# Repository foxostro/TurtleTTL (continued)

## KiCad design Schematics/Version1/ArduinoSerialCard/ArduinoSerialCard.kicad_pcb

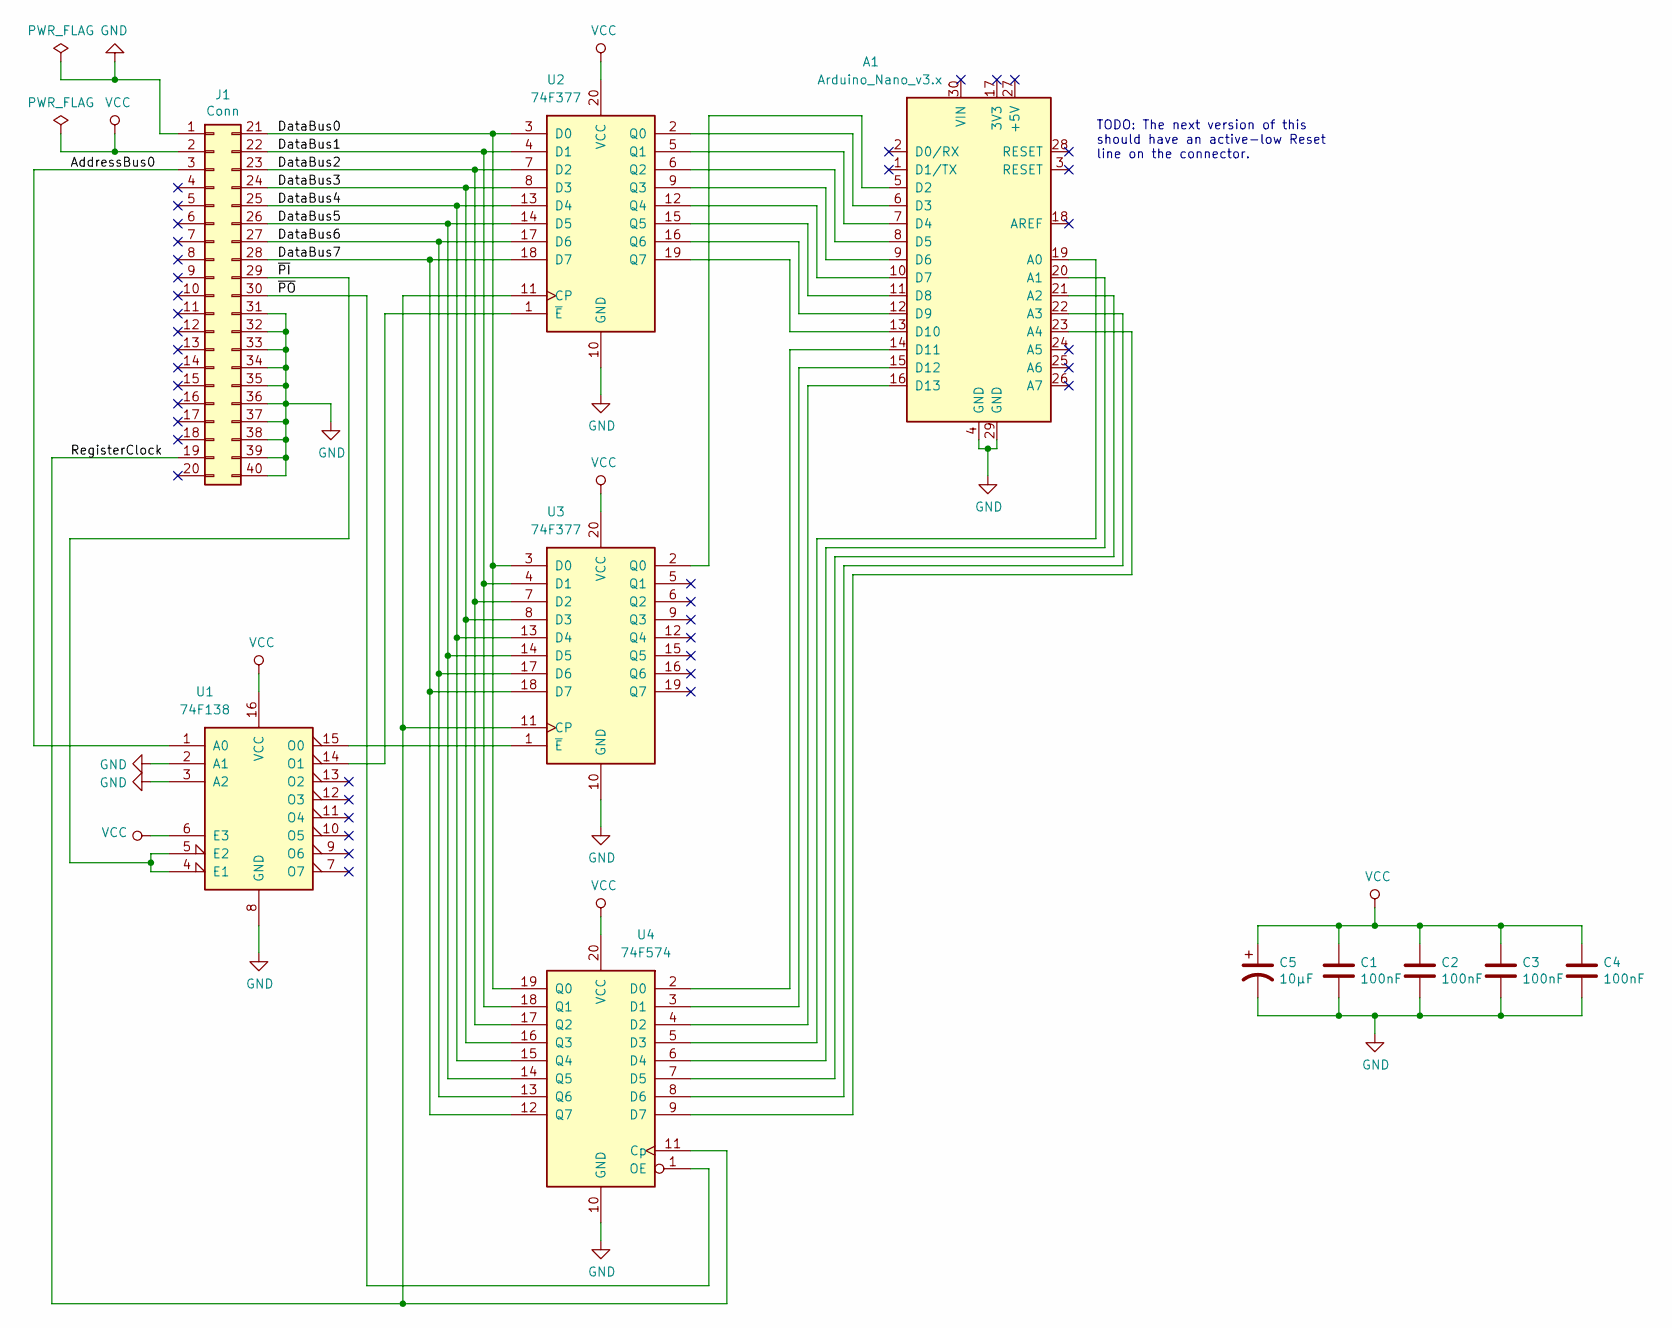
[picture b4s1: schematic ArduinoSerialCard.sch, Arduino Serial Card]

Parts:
A1: Arduino_Nano_v3.x; Arduino_Nano
C1, C2, C3, C4: 100nF; C_Disc_D4.3mm_W1.9mm_P5.00mm
C5: 10µF; CP_Radial_D5.0mm_P2.00mm
J1: Conn; PinSocket_2x20_P2.54mm_Vertical
U1: 74F138; DIP-16_W7.62mm
U2, U3: 74F377; DIP-20_W7.62mm
U4: 74F574; DIP-20_W7.62mm

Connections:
/AddressBus0: J1.3, U1.1 (A0)
/DataBus0: J1.21, U2.3 (D0), U3.3 (D0), U4.19 (Q0)
/DataBus1: J1.22, U2.4 (D1), U3.4 (D1), U4.18 (Q1)
/DataBus2: J1.23, U2.7 (D2), U3.7 (D2), U4.17 (Q2)
/DataBus3: J1.24, U2.8 (D3), U3.8 (D3), U4.16 (Q3)
/DataBus4: J1.25, U2.13 (D4), U3.13 (D4), U4.15 (Q4)
/DataBus5: J1.26, U2.14 (D5), U3.14 (D5), U4.14 (Q5)
/DataBus6: J1.27, U2.17 (D6), U3.17 (D6), U4.13 (Q6)
/DataBus7: J1.28, U2.18 (D7), U3.18 (D7), U4.12 (Q7)
/RegisterClock: J1.19, U2.11 (CP), U3.11 (CP), U4.11 (Cp)
/~PI: J1.29, U1.4 (E1), U1.5 (E2)
/~PO: J1.30, U4.1 (OE)
GND: A1.4 (GND), A1.29 (GND), C1.2, C2.2, C3.2, C4.2, C5.2, J1.1, J1.31, J1.32, J1.33, J1.34, J1.35, J1.36, J1.37, J1.38, J1.39, J1.40, U1.2 (A1), U1.3 (A2), U1.8 (GND), U2.10 (GND), U3.10 (GND), U4.10 (GND)
unnamed: A1.5 (D2), U3.2 (Q0)
unnamed: A1.6 (D3), U2.2 (Q0)
unnamed: A1.7 (D4), U2.5 (Q1)
unnamed: A1.8 (D5), U2.6 (Q2)
unnamed: A1.9 (D6), U2.9 (Q3)
unnamed: A1.10 (D7), U2.12 (Q4)
unnamed: A1.11 (D8), U2.15 (Q5)
unnamed: A1.12 (D9), U2.16 (Q6)
unnamed: A1.13 (D10), U2.19 (Q7)
unnamed: A1.14 (D11), U4.2 (D0)
unnamed: A1.15 (D12), U4.3 (D1)
unnamed: A1.16 (D13), U4.4 (D2)
unnamed: A1.19 (A0), U4.5 (D3)
unnamed: A1.20 (A1), U4.6 (D4)
unnamed: A1.21 (A2), U4.7 (D5)
unnamed: A1.22 (A3), U4.8 (D6)
unnamed: A1.23 (A4), U4.9 (D7)
unnamed: U1.14 (O1), U2.1 (~E)
unnamed: U1.15 (O0), U3.1 (~E)
VCC: C1.1, C2.1, C3.1, C4.1, C5.1, J1.2, U1.6 (E3), U1.16 (VCC), U2.20 (VCC), U3.20 (VCC), U4.20 (VCC)

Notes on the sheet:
TODO: The next version of this should have an active-low Reset line on the connector.

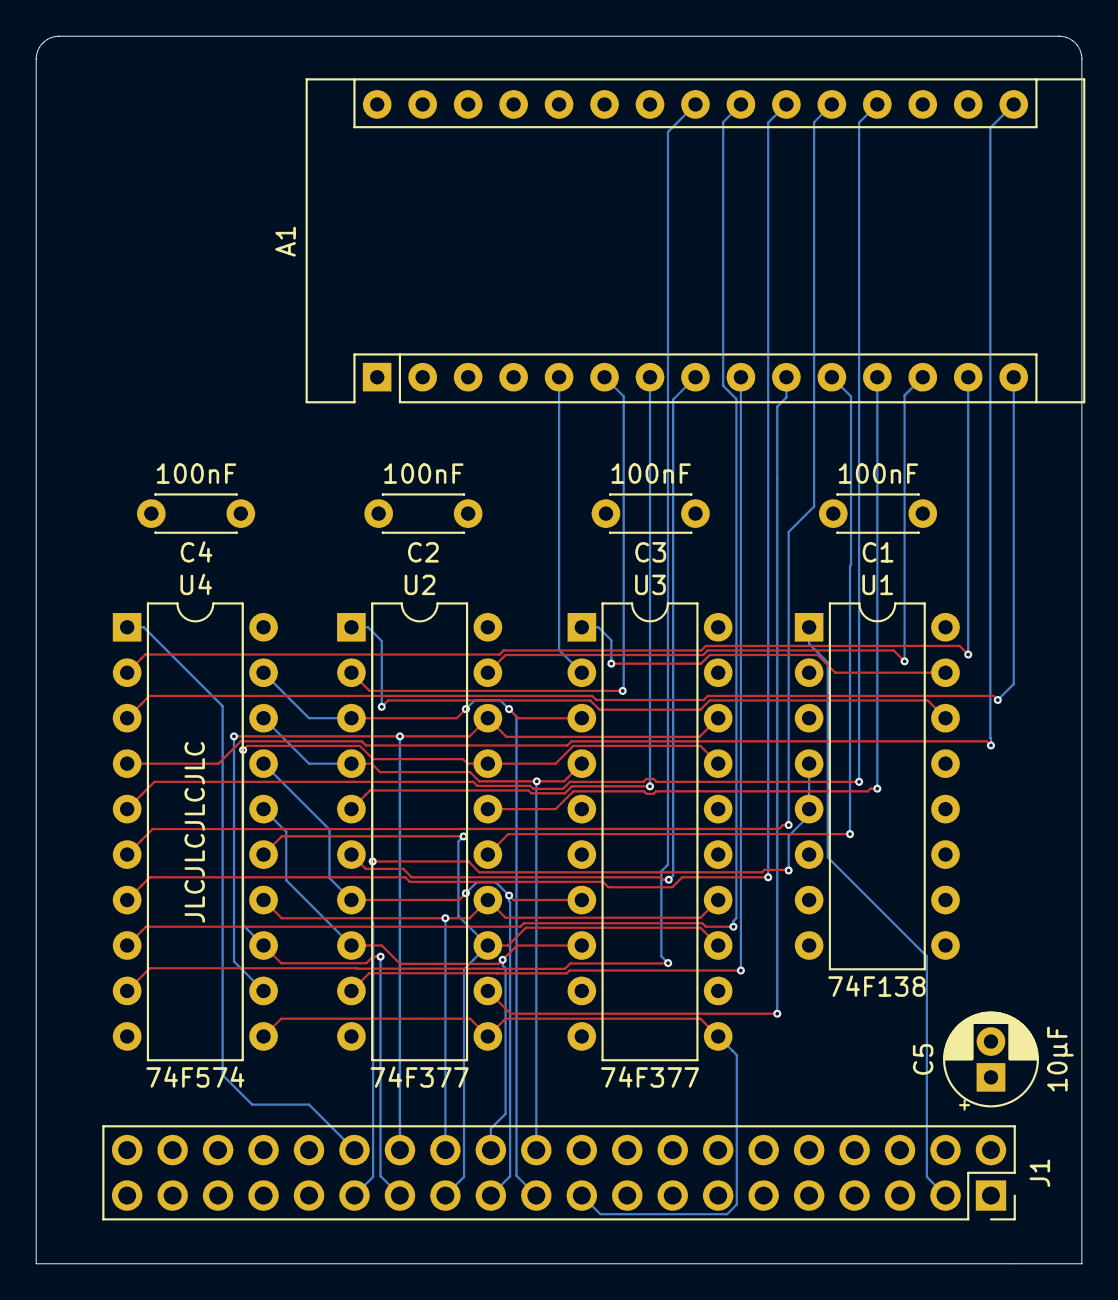
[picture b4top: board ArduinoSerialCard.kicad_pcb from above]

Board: 4 copper layers, 58.4 x 68.6 mm, 11 parts (0 on the bottom side), 33 nets.

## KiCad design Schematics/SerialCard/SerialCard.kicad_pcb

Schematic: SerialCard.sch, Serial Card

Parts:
A1: Arduino_Nano_v3.x; Arduino_Nano
C1: 100nF; C_Disc_D4.3mm_W1.9mm_P5.00mm
J1: Conn; PinSocket_2x20_P2.54mm_Vertical
U1: IDT7134; DIP-48_W15.24mm

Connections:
/Addr0: A1.7 (D4), U1.42
/Addr1: A1.8 (D5), U1.41
/Addr2: A1.9 (D6), U1.40
/Addr3: A1.10 (D7), U1.39
/Addr4: A1.11 (D8), U1.38
/Addr5: A1.12 (D9), U1.37
/Addr6: A1.13 (D10), U1.36
/Addr7: A1.14 (D11), U1.35
/Addr8: A1.15 (D12), U1.34
/Addr9: A1.16 (D13), U1.33
/AddressBus0: J1.3, U1.6
/AddressBus1: J1.4, U1.7
/AddressBus2: J1.5, U1.8
/AddressBus3: J1.6, U1.9
/AddressBus4: J1.7, U1.10
/AddressBus5: J1.8, U1.11
/AddressBus6: J1.9, U1.12
/AddressBus7: J1.10, U1.13
/AddressBus8: J1.11, U1.14
/AddressBus9: J1.12, U1.15
/Data0: A1.26 (A7), U1.25
/Data1: A1.25 (A6), U1.26
/Data2: A1.24 (A5), U1.27
/Data3: A1.23 (A4), U1.28
/Data4: A1.22 (A3), U1.29
/Data5: A1.21 (A2), U1.30
/Data6: A1.20 (A1), U1.31
/Data7: A1.19 (A0), U1.32
/DataBus0: J1.21, U1.16
/DataBus1: J1.22, U1.17
/DataBus2: J1.23, U1.18
/DataBus3: J1.24, U1.19
/DataBus4: J1.25, U1.20
/DataBus5: J1.26, U1.21
/DataBus6: J1.27, U1.22
/DataBus7: J1.28, U1.23
/~PI: J1.29, U1.2
/~PO: J1.30, U1.5
GND: A1.4 (GND), A1.18 (AREF), A1.29 (GND), C1.2, J1.1, J1.31, J1.32, J1.33, J1.34, J1.35, J1.36, J1.37, J1.38, J1.39, J1.40, U1.1, U1.3, U1.4, U1.24, U1.44, U1.45, U1.47
unnamed: A1.5 (D2), U1.46
unnamed: A1.6 (D3), U1.43
VCC: A1.30 (VIN), C1.1, J1.2, U1.48

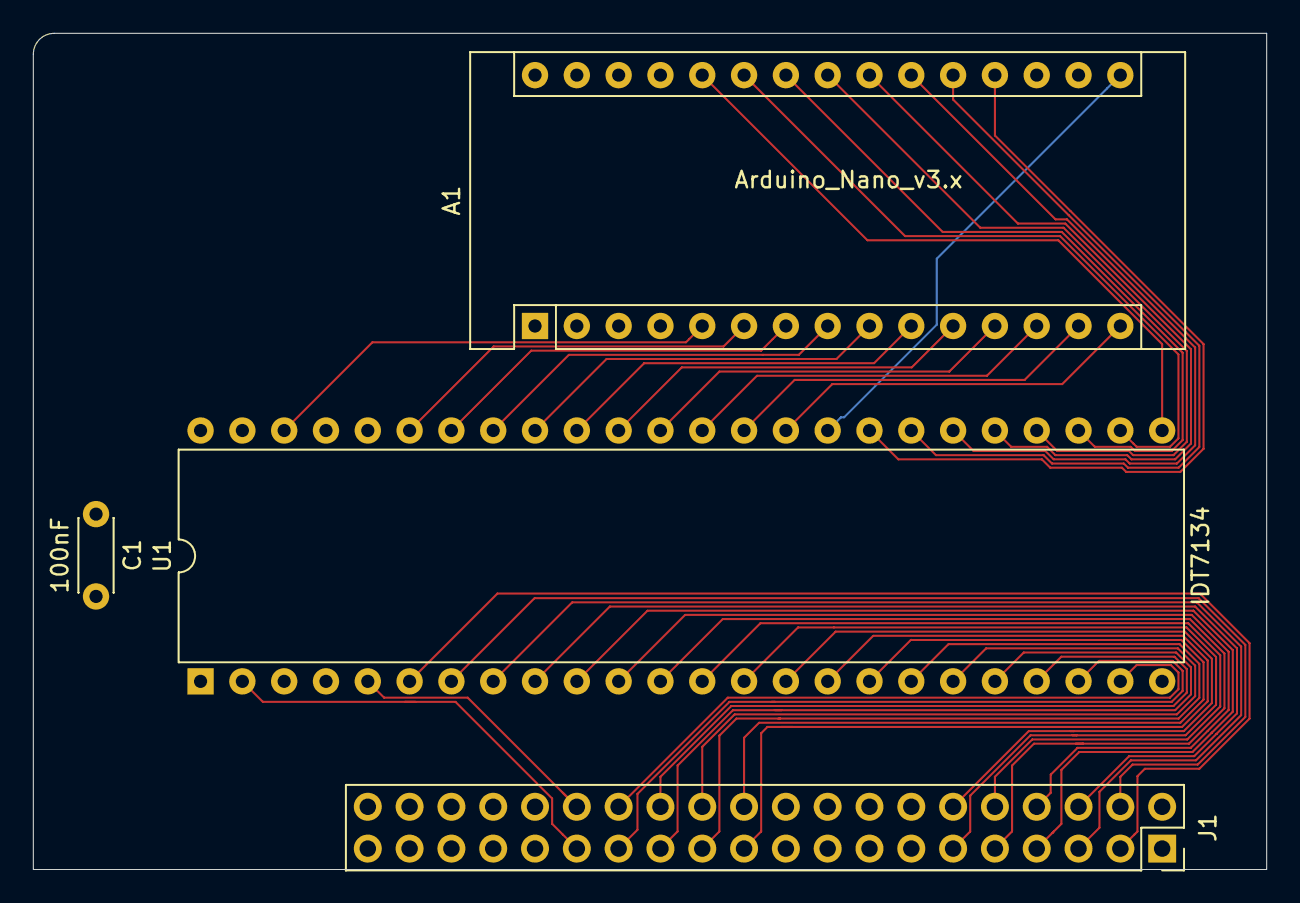
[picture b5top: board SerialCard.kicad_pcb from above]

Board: 4 copper layers, 74.9 x 50.8 mm, 4 parts (0 on the bottom side), 42 nets.

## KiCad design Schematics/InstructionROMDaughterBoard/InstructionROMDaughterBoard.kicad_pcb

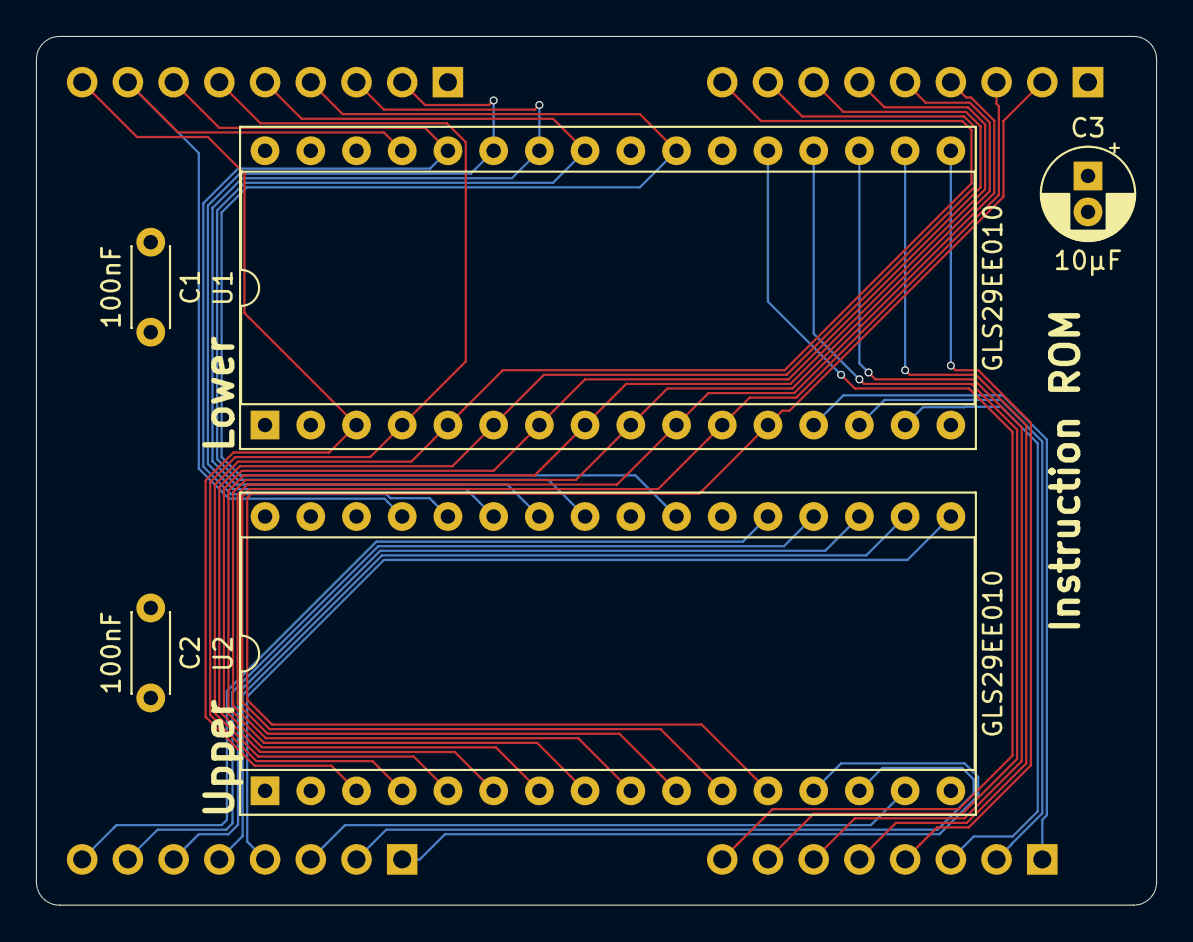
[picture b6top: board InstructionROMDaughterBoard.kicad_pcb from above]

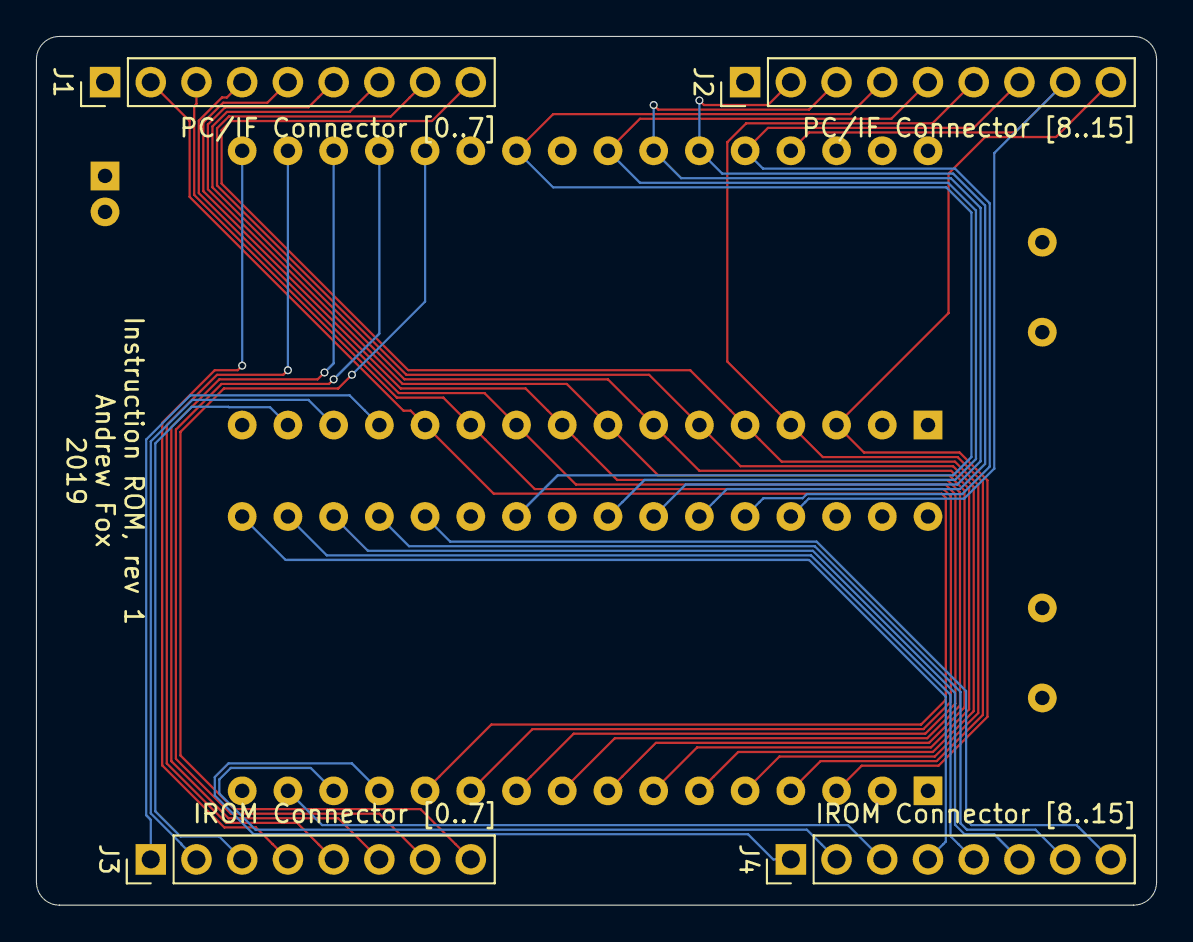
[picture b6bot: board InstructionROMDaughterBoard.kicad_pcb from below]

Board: 4 copper layers, 62.2 x 48.3 mm, 9 parts (4 on the bottom side), 34 nets.

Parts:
C1, C2: 100nF; C_Disc_D4.3mm_W1.9mm_P5.00mm
C3: 10µF; CP_Radial_D5.0mm_P2.00mm
J1: PC/IF Connector [0..7]; PinHeader_1x09_P2.54mm_Vertical
J2: PC/IF Connector [8..15]; PinHeader_1x09_P2.54mm_Vertical
J3: IROM Connector [0..7]; PinHeader_1x08_P2.54mm_Vertical
J4: IROM Connector [8..15]; PinHeader_1x08_P2.54mm_Vertical
U1, U2: GLS29EE010; DIP-32_W15.24mm_Socket

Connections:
/IROM0: J3.1, U1.13
/IROM1: J3.2, U1.14
/IROM2: J3.3, U1.15
/IROM3: J3.4, U1.17
/IROM4: J3.5, U1.18
/IROM5: J3.6, U1.19
/IROM6: J3.7, U1.20
/IROM7: J3.8, U1.21
/IROM8: J4.1, U2.13
/IROM9: J4.2, U2.14
/IROM10: J4.3, U2.15
/IROM11: J4.4, U2.17
/IROM12: J4.5, U2.18
/IROM13: J4.6, U2.19
/IROM14: J4.7, U2.20
/IROM15: J4.8, U2.21
/PC_IF0: J1.2, U1.12, U2.12
/PC_IF1: J1.3, U1.11, U2.11
/PC_IF2: J1.4, U1.10, U2.10
/PC_IF3: J1.5, U1.9, U2.9
/PC_IF4: J1.6, U1.8, U2.8
/PC_IF5: J1.7, U1.7, U2.7
/PC_IF6: J1.8, U1.6, U2.6
/PC_IF7: J1.9, U1.5, U2.5
/PC_IF8: J2.2, U1.27, U2.27
/PC_IF9: J2.3, U1.26, U2.26
/PC_IF10: J2.4, U1.23, U2.23
/PC_IF11: J2.5, U1.25, U2.25
/PC_IF12: J2.6, U1.4, U2.4
/PC_IF13: J2.7, U1.28, U2.28
/PC_IF14: J2.8, U1.29, U2.29
/PC_IF15: J2.9, U1.3, U2.3
GND: C1.2, C2.2, C3.2, J2.1, U1.2, U1.16, U1.22, U1.24, U2.2, U2.16, U2.22, U2.24
VCC: C1.1, C2.1, C3.1, J1.1, U1.31, U1.32, U2.31, U2.32

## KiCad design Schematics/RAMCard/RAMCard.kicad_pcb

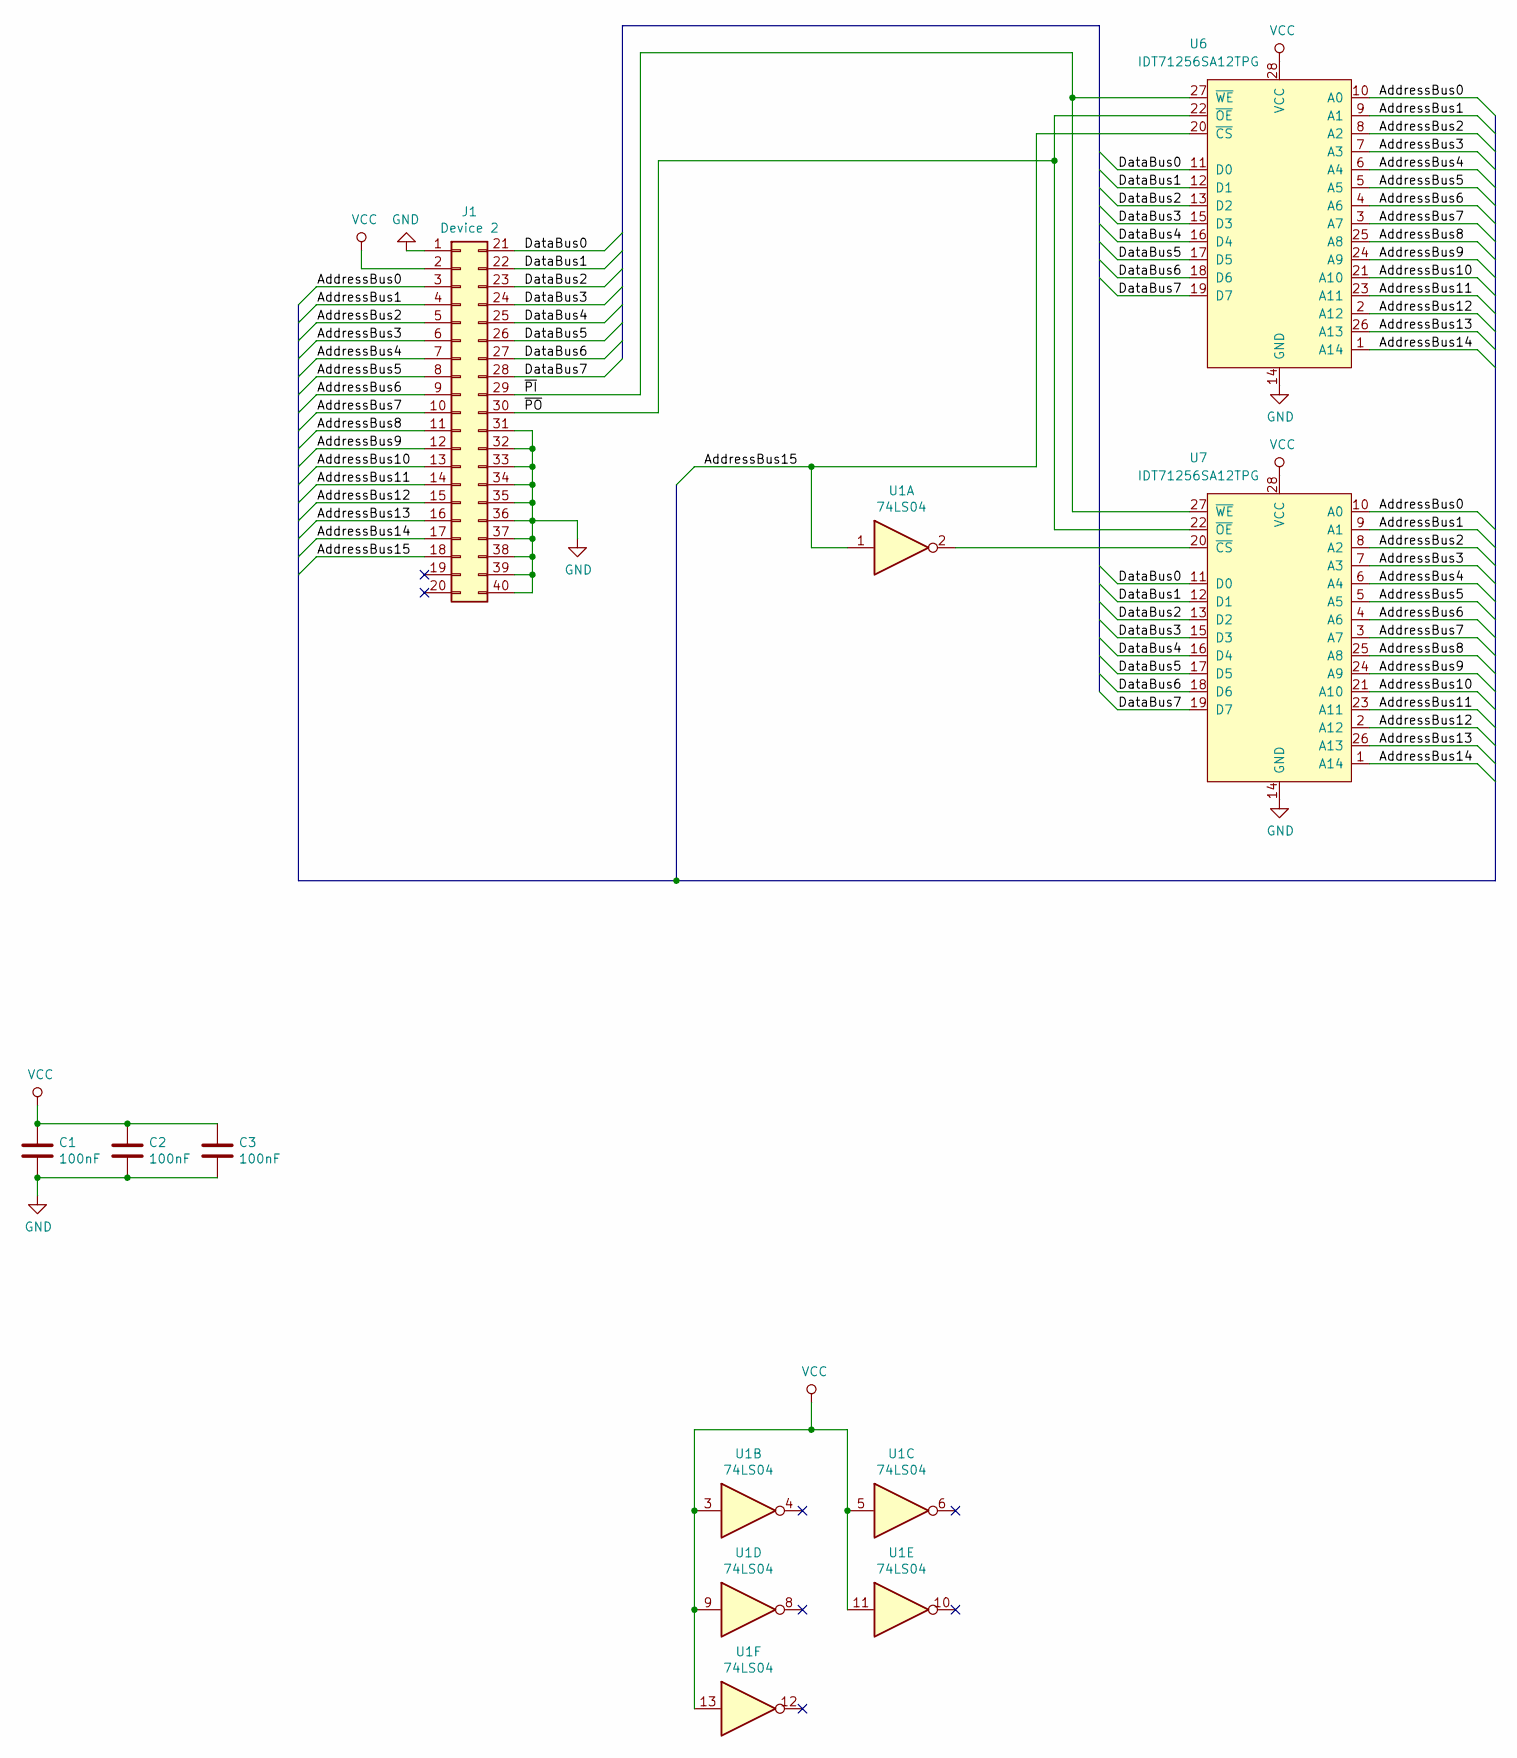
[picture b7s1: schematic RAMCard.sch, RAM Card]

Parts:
C1, C2, C3: 100nF; C_Disc_D4.3mm_W1.9mm_P5.00mm
J1: Device 2; PinHeader_2x20_P2.54mm_Horizontal
U1: 74LS04; DIP-14_W7.62mm
U6, U7: IDT71256SA12TPG; DIP-28_W7.62mm_Socket

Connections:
/AddressBus0: J1.3, U6.10 (A0), U7.10 (A0)
/AddressBus1: J1.4, U6.9 (A1), U7.9 (A1)
/AddressBus2: J1.5, U6.8 (A2), U7.8 (A2)
/AddressBus3: J1.6, U6.7 (A3), U7.7 (A3)
/AddressBus4: J1.7, U6.6 (A4), U7.6 (A4)
/AddressBus5: J1.8, U6.5 (A5), U7.5 (A5)
/AddressBus6: J1.9, U6.4 (A6), U7.4 (A6)
/AddressBus7: J1.10, U6.3 (A7), U7.3 (A7)
/AddressBus8: J1.11, U6.25 (A8), U7.25 (A8)
/AddressBus9: J1.12, U6.24 (A9), U7.24 (A9)
/AddressBus10: J1.13, U6.21 (A10), U7.21 (A10)
/AddressBus11: J1.14, U6.23 (A11), U7.23 (A11)
/AddressBus12: J1.15, U6.2 (A12), U7.2 (A12)
/AddressBus13: J1.16, U6.26 (A13), U7.26 (A13)
/AddressBus14: J1.17, U6.1 (A14), U7.1 (A14)
/AddressBus15: J1.18, U1.1, U6.20 (~CS)
/DataBus0: J1.21, U6.11 (D0), U7.11 (D0)
/DataBus1: J1.22, U6.12 (D1), U7.12 (D1)
/DataBus2: J1.23, U6.13 (D2), U7.13 (D2)
/DataBus3: J1.24, U6.15 (D3), U7.15 (D3)
/DataBus4: J1.25, U6.16 (D4), U7.16 (D4)
/DataBus5: J1.26, U6.17 (D5), U7.17 (D5)
/DataBus6: J1.27, U6.18 (D6), U7.18 (D6)
/DataBus7: J1.28, U6.19 (D7), U7.19 (D7)
/~PI: J1.29, U6.27 (~WE), U7.27 (~WE)
/~PO: J1.30, U6.22 (~OE), U7.22 (~OE)
GND: C1.2, C2.2, C3.2, J1.1, J1.31, J1.32, J1.33, J1.34, J1.35, J1.36, J1.37, J1.38, J1.39, J1.40, U6.14 (GND), U7.14 (GND)
unnamed: U1.2, U7.20 (~CS)
VCC: C1.1, C2.1, C3.1, J1.2, U1.3, U1.5, U1.9, U1.11, U1.13, U6.28 (VCC), U7.28 (VCC)

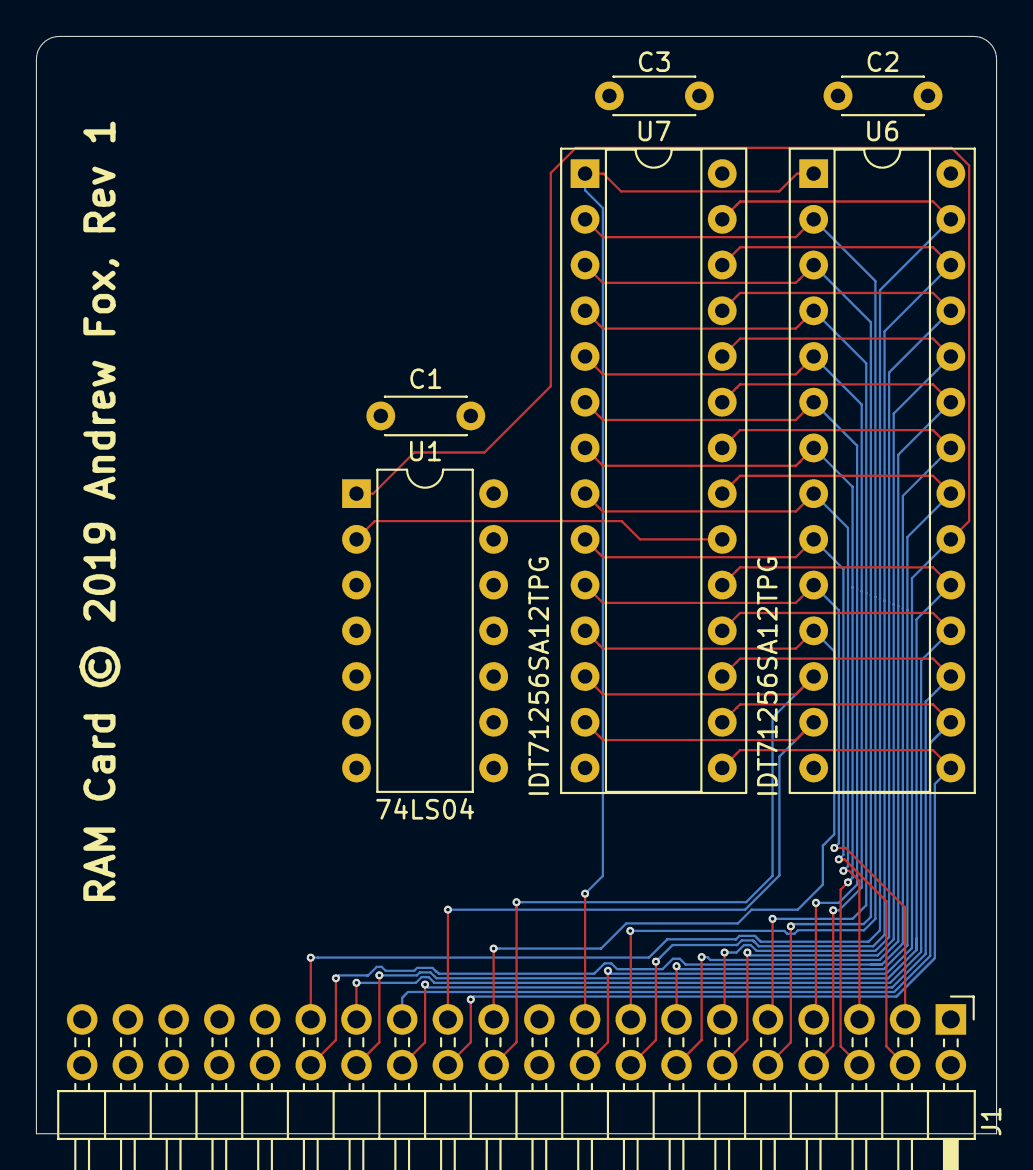
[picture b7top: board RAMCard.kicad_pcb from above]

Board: 4 copper layers, 53.3 x 61.0 mm, 7 parts (0 on the bottom side), 29 nets.

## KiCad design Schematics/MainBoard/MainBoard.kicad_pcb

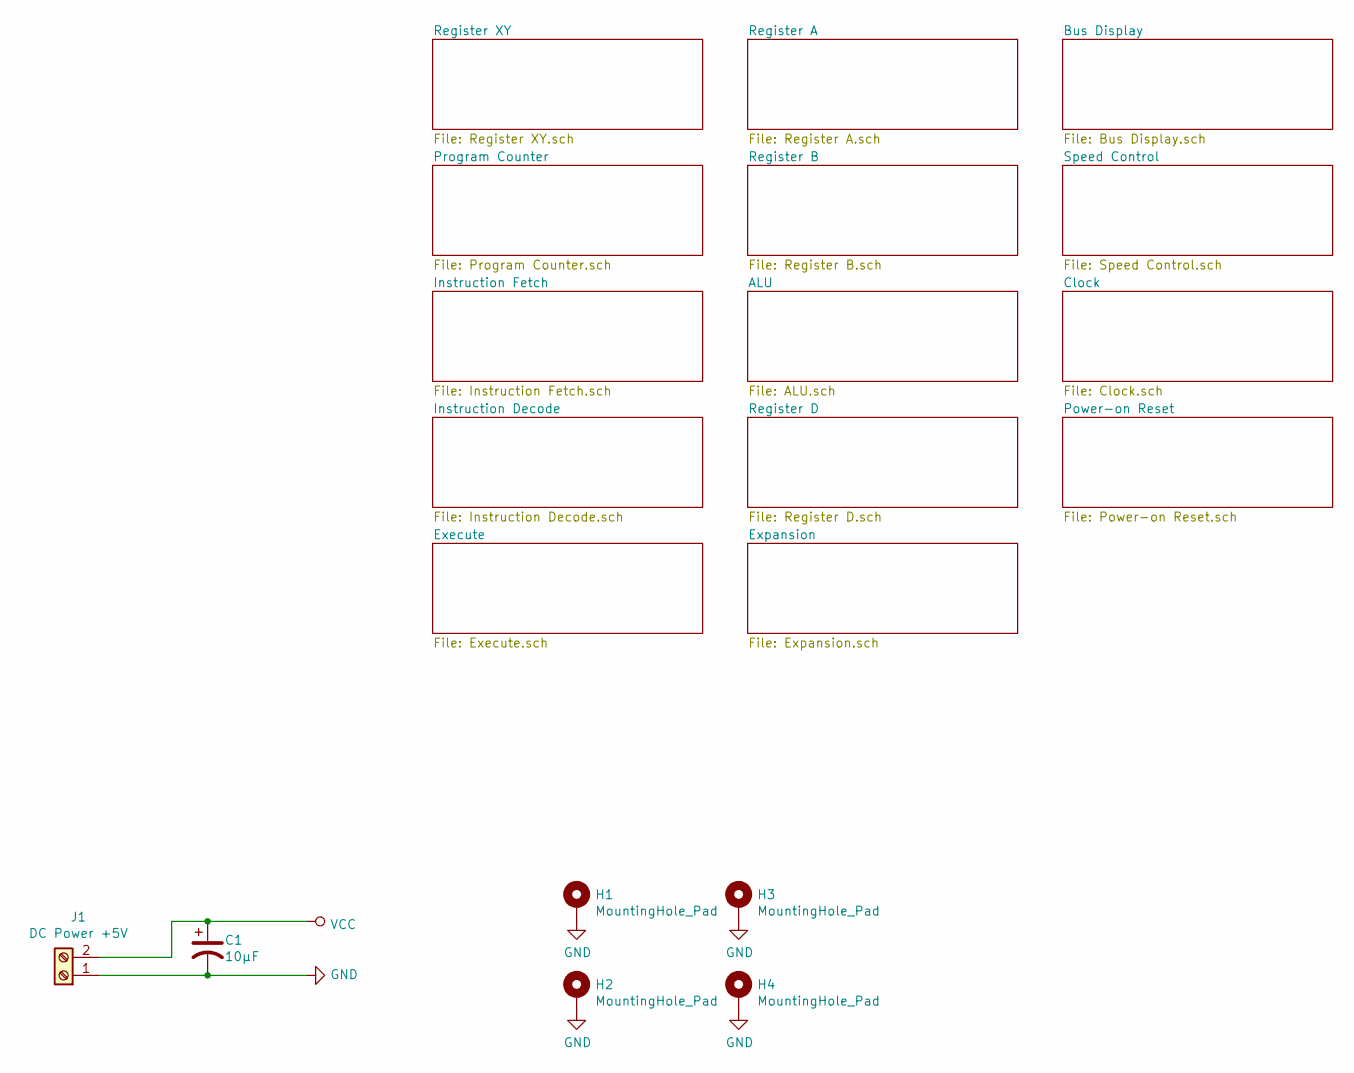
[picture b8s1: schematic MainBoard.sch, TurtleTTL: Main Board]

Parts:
C1: 10µF; CP_Radial_D5.0mm_P2.00mm
H1, H2, H3, H4: MountingHole_Pad; MountingHole_3.2mm_M3_Pad
J1: DC Power +5V; TerminalBlock_MetzConnect_Type055_RT01502HDWU_1x02_P5.00mm_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

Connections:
GND: C1.2, H1.1, H2.1, H3.1, H4.1, J1.1; also elsewhere on the board
VCC: C1.1, J1.2; also elsewhere on the board

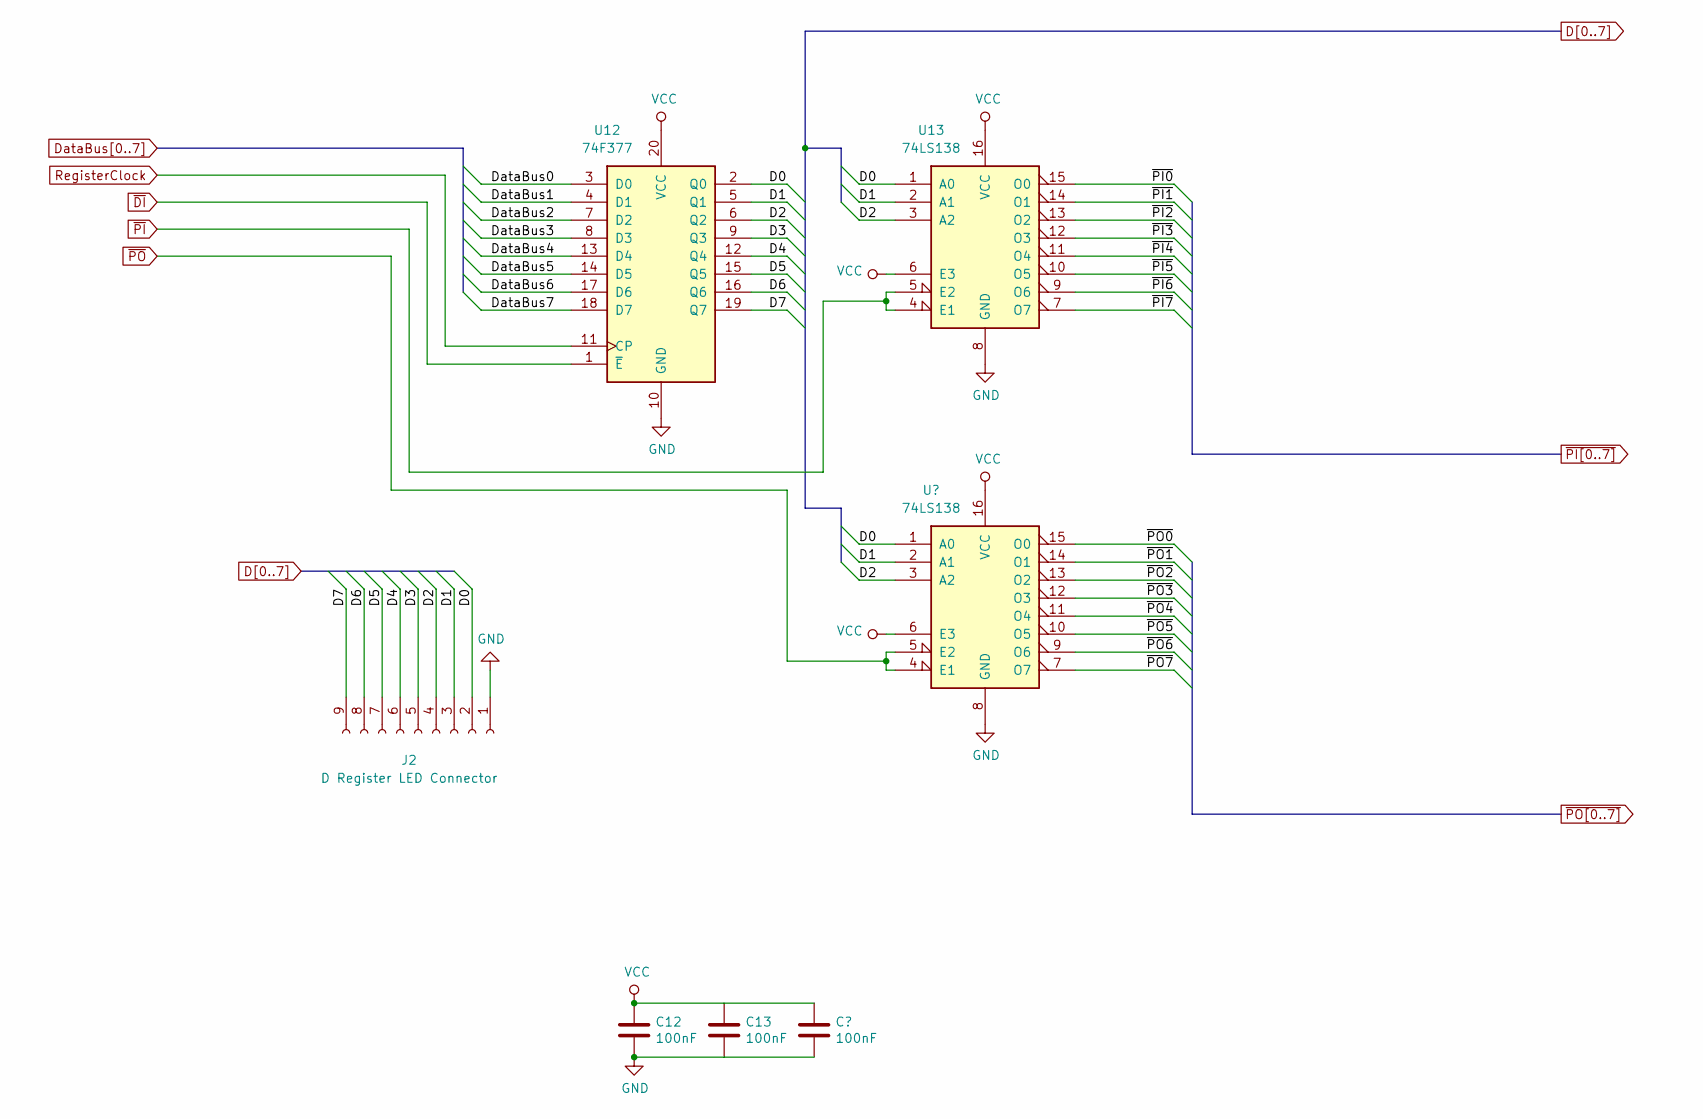
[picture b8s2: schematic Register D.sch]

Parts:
C12, C13: 100nF; C_Disc_D4.3mm_W1.9mm_P5.00mm
J2: D Register LED Connector; PinSocket_1x09_P2.54mm_Vertical
U12: 74F377; DIP-20_W7.62mm
U13: 74LS138; DIP-16_W7.62mm

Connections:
D0: J2.2, U12.2 (Q0), U13.1 (A0); also elsewhere on the board
D1: J2.3, U12.5 (Q1), U13.2 (A1); also elsewhere on the board
D2: J2.4, U12.6 (Q2), U13.3 (A2); also elsewhere on the board
D3: J2.5, U12.9 (Q3)
D4: J2.6, U12.12 (Q4)
D5: J2.7, U12.15 (Q5)
D6: J2.8, U12.16 (Q6)
D7: J2.9, U12.19 (Q7)
DataBus0: U12.3 (D0); also elsewhere on the board
DataBus1: U12.4 (D1); also elsewhere on the board
DataBus2: U12.7 (D2); also elsewhere on the board
DataBus3: U12.8 (D3); also elsewhere on the board
DataBus4: U12.13 (D4); also elsewhere on the board
DataBus5: U12.14 (D5); also elsewhere on the board
DataBus6: U12.17 (D6); also elsewhere on the board
DataBus7: U12.18 (D7); also elsewhere on the board
GND: C12.2, C13.2, J2.1, U12.10 (GND), U13.8 (GND); also elsewhere on the board
RegisterClock: U12.11 (CP); also elsewhere on the board
VCC: C12.1, C13.1, U12.20 (VCC), U13.6 (E3), U13.16 (VCC); also elsewhere on the board
~DI: U12.1 (~E); also elsewhere on the board
~PI: U13.4 (E1), U13.5 (E2); also elsewhere on the board
~PI0: U13.15 (O0); also elsewhere on the board
~PI1: U13.14 (O1); also elsewhere on the board
~PI2: U13.13 (O2); also elsewhere on the board
~PI3: U13.12 (O3); also elsewhere on the board
~PI4: U13.11 (O4); also elsewhere on the board
~PI5: U13.10 (O5); also elsewhere on the board
~PI6: U13.9 (O6); also elsewhere on the board
~PI7: U13.7 (O7); also elsewhere on the board

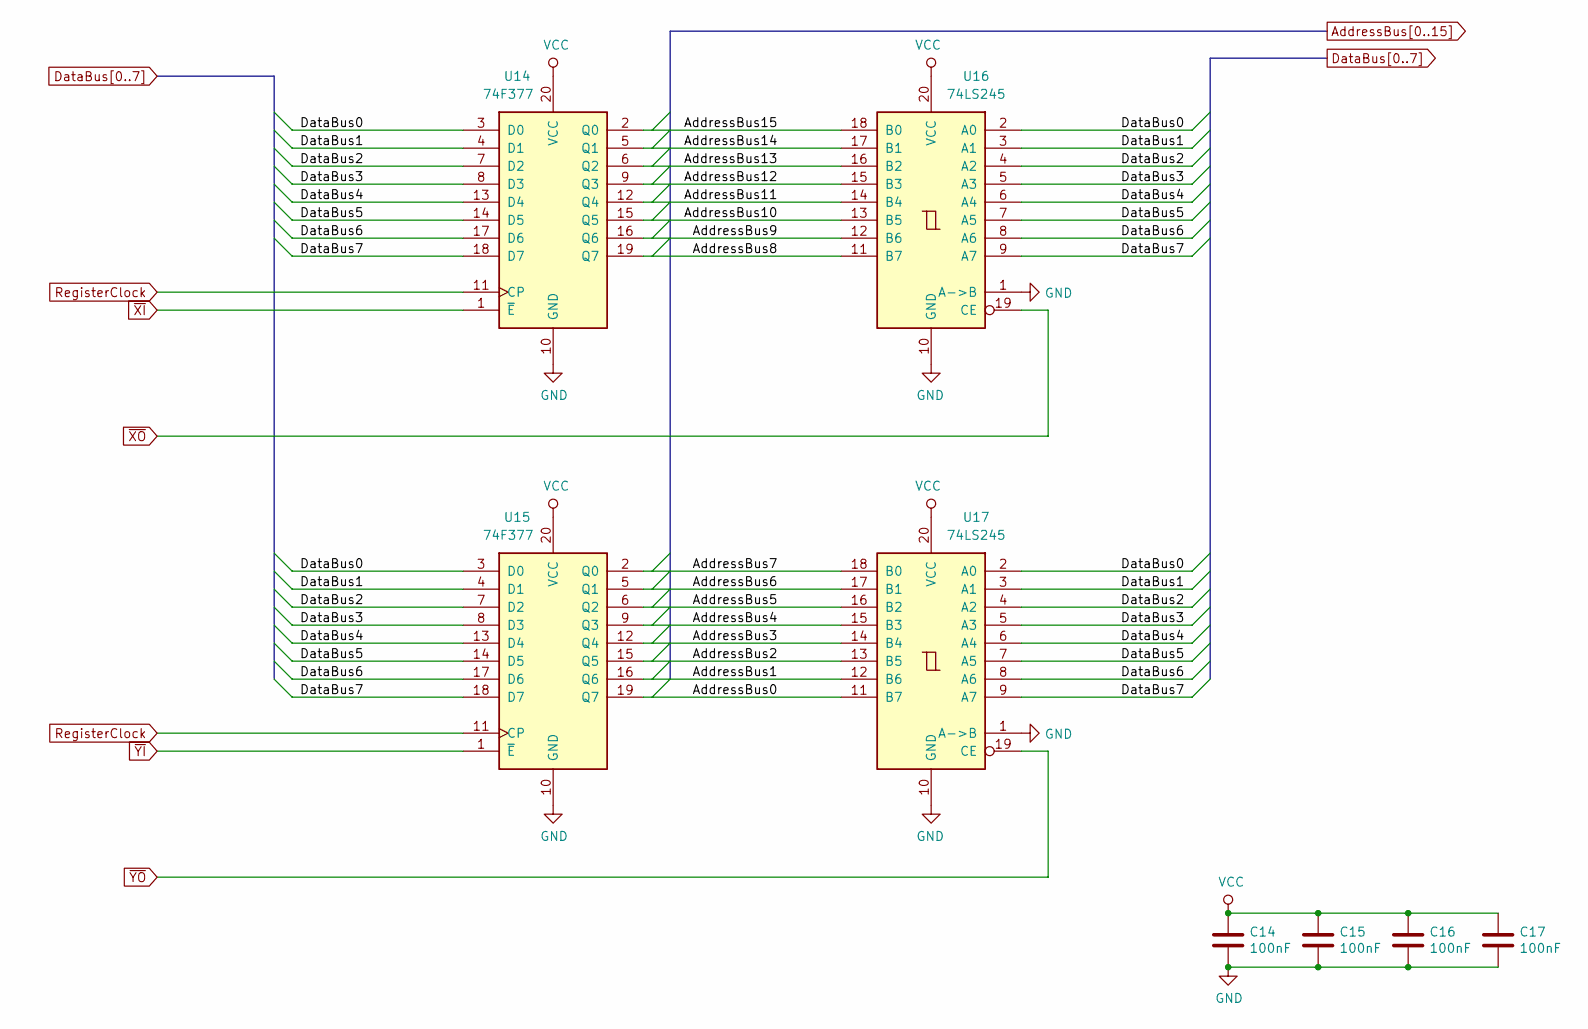
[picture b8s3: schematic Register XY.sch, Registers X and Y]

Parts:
C14, C15, C16, C17: 100nF; C_Disc_D4.3mm_W1.9mm_P5.00mm
U14, U15: 74F377; DIP-20_W7.62mm
U16, U17: 74LS245; DIP-20_W7.62mm_Socket

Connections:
AddressBus0: U15.19 (Q7), U17.11 (B7); also elsewhere on the board
AddressBus1: U15.16 (Q6), U17.12 (B6); also elsewhere on the board
AddressBus2: U15.15 (Q5), U17.13 (B5); also elsewhere on the board
AddressBus3: U15.12 (Q4), U17.14 (B4); also elsewhere on the board
AddressBus4: U15.9 (Q3), U17.15 (B3); also elsewhere on the board
AddressBus5: U15.6 (Q2), U17.16 (B2); also elsewhere on the board
AddressBus6: U15.5 (Q1), U17.17 (B1); also elsewhere on the board
AddressBus7: U15.2 (Q0), U17.18 (B0); also elsewhere on the board
AddressBus8: U14.19 (Q7), U16.11 (B7); also elsewhere on the board
AddressBus9: U14.16 (Q6), U16.12 (B6); also elsewhere on the board
AddressBus10: U14.15 (Q5), U16.13 (B5); also elsewhere on the board
AddressBus11: U14.12 (Q4), U16.14 (B4); also elsewhere on the board
AddressBus12: U14.9 (Q3), U16.15 (B3); also elsewhere on the board
AddressBus13: U14.6 (Q2), U16.16 (B2); also elsewhere on the board
AddressBus14: U14.5 (Q1), U16.17 (B1); also elsewhere on the board
AddressBus15: U14.2 (Q0), U16.18 (B0); also elsewhere on the board
DataBus0: U14.3 (D0), U15.3 (D0), U16.2 (A0), U17.2 (A0); also elsewhere on the board
DataBus1: U14.4 (D1), U15.4 (D1), U16.3 (A1), U17.3 (A1); also elsewhere on the board
DataBus2: U14.7 (D2), U15.7 (D2), U16.4 (A2), U17.4 (A2); also elsewhere on the board
DataBus3: U14.8 (D3), U15.8 (D3), U16.5 (A3), U17.5 (A3); also elsewhere on the board
DataBus4: U14.13 (D4), U15.13 (D4), U16.6 (A4), U17.6 (A4); also elsewhere on the board
DataBus5: U14.14 (D5), U15.14 (D5), U16.7 (A5), U17.7 (A5); also elsewhere on the board
DataBus6: U14.17 (D6), U15.17 (D6), U16.8 (A6), U17.8 (A6); also elsewhere on the board
DataBus7: U14.18 (D7), U15.18 (D7), U16.9 (A7), U17.9 (A7); also elsewhere on the board
GND: C14.2, C15.2, C16.2, C17.2, U14.10 (GND), U15.10 (GND), U16.1 (A->B), U16.10 (GND), U17.1 (A->B), U17.10 (GND); also elsewhere on the board
RegisterClock: U14.11 (CP), U15.11 (CP); also elsewhere on the board
VCC: C14.1, C15.1, C16.1, C17.1, U14.20 (VCC), U15.20 (VCC), U16.20 (VCC), U17.20 (VCC); also elsewhere on the board
~XI: U14.1 (~E); also elsewhere on the board
~XO: U16.19 (CE); also elsewhere on the board
~YI: U15.1 (~E); also elsewhere on the board
~YO: U17.19 (CE); also elsewhere on the board
